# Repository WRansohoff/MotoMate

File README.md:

# "MotoMate" Handheld GPS Receiver

This is a small board designed to act as a handheld GPS receiver, and eventually (I hope) a handlebar-mounted GPS mapper / tracker for offroad motorcycling.

# Details

The microcontroller core is an STM32L496Rx chip - I recommend the STM32L496RGT3, because it costs less than $1 to get an extra 512KB of Flash (although the chip itself is more like $10). The 320KB of built-in RAM is enough to store a 150KB framebuffer for the 320x240 16bpp ILI9341 display, but it doesn't leave much room for storage-intensive algorithms such as image processing. Still, there's no external storage to worry about besides the microSD card.

The board is wired to use hardware periphererals for driving the SD/MMC interface, USB OTG, SPI for the display, and UART for talking to a "GY-NEO6MV2" GPS module. I've noticed that some listings for these u-blox Neo-6M-based GPS modules have red-colored boards with pinouts that won't work with this design; look for blue-colored ones and double-check the pinouts against the schematic. I might update the design to use the module itself instead of a cheap breakout board in the future, but for now, sorry for the inconvenience.

There's also a single-channel audio amplifier connected to one of the chip's DACs with a mute switch, and some ADCs are used to monitor a photodiode and the board's battery voltage. And there are pads exposed for an extra UART and I2C connection, and seven button inputs split across two tactile buttons and a 'navigation switch'. The buttons are assigned to pins so that there shouldn't be any conflicts with EXTI lines when setting up interrupts to listen for presses.

I'll write up more comprehensive information (and upload some proper gerber files) once I've had a chance to test this revision and upload some basic test firmwares to confirm the board's various functions.

# Schematic and Board Renders

# Previous Revision

I've assembled an earlier version of this design and confirmed that most parts of the design work, but I haven't written a comprehensive "GPS mapper" firmware yet. The first version has too much space between the TFT ribbon connector and the edge of the board to fold the display over the USB connector and mute switch, so it was awkward to handle. I hope that this version will fit together better, but I haven't received it yet for testing.

Sorry that I didn't get a better picture of the lit-up TFT; it's hard to take pictures of backlit displays, and it's not that important anyways. I also edited one of the images to remove the actual GPS coordinates, because I didn't feel like driving out to the middle of the woods to take a picture.

Anyways, so far I've tested (or not) the following parts:

* Battery monitoring: the 'charging' and 'done' LEDs seem to reflect the charge status, and the 12-bit ADC reads close to 4.2V on a full charge using the formula: `VBatt = ( ADC * 2 / 4095 ) * 3.3`. Note that for an accurate reading, you need to set one of the highest sampling times (250-650 cycles) due to the low amount of current flowing through the voltage divider.

* TFT display: The backlight can be adjusted with a PWM signal, and the SPI peripheral can be used with DMA to draw a framebuffer to the display. This makes it much easier to test other parts of the board :)

* GPS module: Appears to work, although I haven't tried configuring it with anything other than the default settings. After placing the antenna with a clear view of the sky and letting it acquire a few satellites, it reports latitude and longitude readings that appear to be accurate to within maybe 5 meters or so.

* microSD card: Not tested.

* Buttons: Tested using falling-edge interrupts with the pins configured as inputs with pull-up resistors enabled. These low-profile buttons are really designed to be used with a case that has plastic or rubber 'pegs' connected to larger buttons, though.

* Auxiliary UARTs and I2C: Not tested.

* 'Heartbeat' LED: Works.

* Photodiode: Not tested; in the first revision of the board, I put the photodiode underneath where the display's ribbon connector folded over, so it was always in darkness. D'oh!

* Speaker: Works well enough to play a sine wave accurately enough for a tuner to read the desired note. I haven't tried playing music or speech though, and it probably wouldn't do that very well. This is only a 12-bit DAC with poor filtering, after all. The speaker is mostly intended for beeps, buzzes, and chirps.

See `firmware/` for the source code used to run those tests, and `fw_lib/` for some shared helper functions.

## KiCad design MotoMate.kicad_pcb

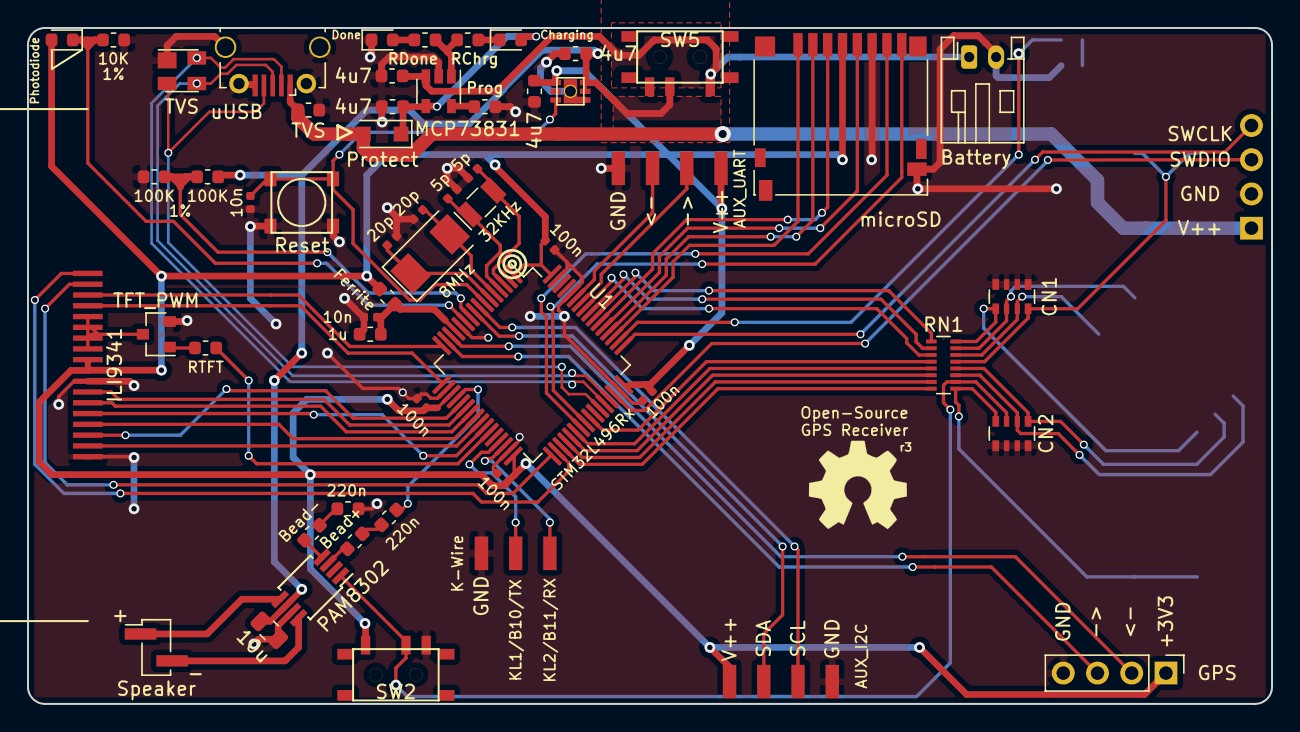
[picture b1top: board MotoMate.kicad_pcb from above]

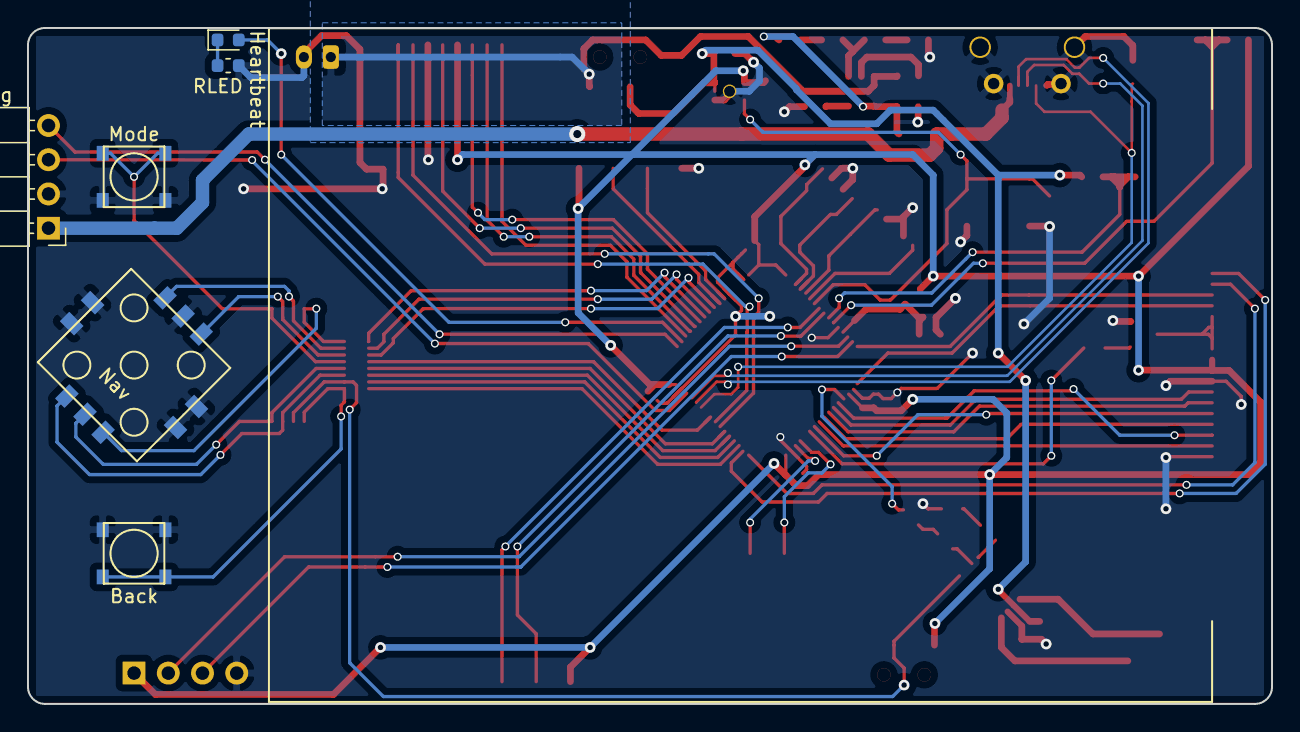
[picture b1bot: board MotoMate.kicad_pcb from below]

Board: 2 copper layers, 92.3 x 50.2 mm, 62 parts (6 on the bottom side), 75 nets.

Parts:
C1, C2, C19, C20: 4u7; C_0603_1608Metric
C3, C4, C5, C6: 100n; C_0402_1005Metric
C7, C13: 10n; C_0402_1005Metric
C8: 1u; C_0603_1608Metric
C9, C10: 20p; C_0402_1005Metric
C11, C12: 5p; C_0402_1005Metric
C16, C17: 220n; C_0603_1608Metric
C18: 10u; C_0805_2012Metric
CN1: Cin1; R_Array_Convex_4x0603
CN2: Cin2; R_Array_Convex_4x0603
D1: TVS; SOT-143
D2: Photodiode; LED_0603_1608Metric
D3: Heartbeat; LED_0603_1608Metric
D4: Protect; D_SOD-123F
D5: Charging; LED_0603_1608Metric
D6: Done; LED_0603_1608Metric
FB1: Ferrite; R_0603_1608Metric
FB2: Bead+; R_0603_1608Metric
FB3: Bead-; R_0603_1608Metric
J1: Prog; PinHeader_1x04_P2.54mm_Horizontal
J2: uUSB; MyMicroUSB
J3: microSD; microSD_HC_Hirose_DM3D-SF
J4: GPS; PinHeader_1x04_P2.54mm_Vertical
J5: AUX_UART; Conn_01x04_H_SMD
J6: AUX_I2C; Conn_01x04_H_SMD
J7: Battery; JST_PH_S2B-PH-K_1x02_P2.00mm_Horizontal
J8: ILI9341; ILI9341_18P_0.8mm
J9: K-Wire; Conn_01x03_H_SMD
LS1: Speaker; PinHeader_1x02_P2.00mm_Vertical_SMD_Pin1Left
Q1: TFT_PWM; SOT-23
R1: RTFT; R_0603_1608Metric
R2, R3: 100K; R_0603_1608Metric
R4: 10K; R_0603_1608Metric
R5: Prog; R_0603_1608Metric
R6: RChrg; R_0603_1608Metric
R7: RDone; R_0603_1608Metric
R8: RLED; R_0603_1608Metric
RN1: Rin; R_Array_Convex_8x0602
RV1: TVS; R_0603_1608Metric
SW1: Reset; Snap_Tac_Switch_SMT
SW2: Mute; mini_slide_switch
SW3: Mode; Snap_Tac_Switch_SMT
SW4: Back; Snap_Tac_Switch_SMT
SW5: On/Off; mini_slide_switch
SW6: Nav; NavSwitch_SMT
U1: STM32L496Rx; LQFP-64_10x10mm_P0.5mm
U2: LDFM33; ST_LDFM_2x2DFN
U3: PAM8302; MSOP-8_3x3mm_P0.65mm
U4: MCP73831; SOT-23-5
Y1: 8MHz; Crystal_SMD_Abracon_ABM3-2Pin_5.0x3.2mm
Y2: 32KHz; Crystal_SMD_EuroQuartz_EQ161-2Pin_3.2x1.5mm

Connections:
+5V: D4.2, J1.1, J2.1, RV1.1
+BATT: C20.1, J7.1, SW5.1, U4.3
Aux_RX: J5.2, U1.58
Aux_SCL: J6.3, U1.8
Aux_SDA: J6.2, U1.9
Aux_TX: J5.3, U1.59
Back: RN1.8, U1.35
BackR: CN2.8, RN1.9, SW4.1
Battery_Check: R2.1, R3.2, U1.10
GND: C1.2, C2.1, C3.2, C4.1, C5.1, C6.2, C7.1, C8.2, C9.2, C10.1, C11.2, C12.1, C13.2, C17.2, C18.2, C19.1, C20.2, CN1.1, CN1.2, CN1.3, CN1.4, CN2.1, CN2.2, CN2.3, CN2.4, D1.1, D6.1, J1.2, J2.5, J2.6, J3.6, J3.9, J4.4, J5.4, J6.4, J7.2, J8.1, J8.8, J9.3, Q1.2, R3.1, R4.2, R5.2, R8.2, RV1.2, SW1.1, SW2.3, SW3.2, SW4.2, SW6.6, U1.12, U1.18, U1.31, U1.47, U1.60, U1.63, U2.4, U2.7, U3.7, U4.2
GPS_RX: J4.2, U1.14
GPS_TX: J4.3, U1.15
Heartbeat: D3.2, U1.50
K-Line1: J9.2, U1.29
K-Line2: J9.1, U1.30
Light_Sensor: D2.1, R4.1, U1.11
Mode: RN1.4, U1.41
ModeR: CN1.8, RN1.13, SW3.1
Mute: RN1.7, U1.36
MuteR: CN2.7, RN1.10, SW2.2, U3.1
NavDR: CN1.6, RN1.15, SW6.4
NavLR: CN2.6, RN1.11, SW6.3
NavPR: CN2.5, RN1.12, SW6.2
NavRR: CN1.7, RN1.14, SW6.5
NavUR: CN1.5, RN1.16, SW6.1
Nav_D: RN1.2, U1.56
Nav_L: RN1.6, U1.37
Nav_P: RN1.5, U1.38
Nav_R: RN1.3, U1.57
Nav_U: RN1.1, U1.55
unnamed: C7.2, C8.1, FB1.1, U1.13
unnamed: C9.1, U1.6, Y1.1
unnamed: C10.2, U1.5, Y1.2
unnamed: C11.1, U1.4, Y2.1
unnamed: C12.2, U1.3, Y2.2
unnamed: C16.1, FB2.2
unnamed: C17.1, FB3.1
unnamed: D3.1, R8.1
unnamed: D5.1, R6.1
unnamed: D6.2, R7.1
unnamed: FB2.1, U3.3
unnamed: FB3.2, U3.4
unnamed: J8.11, J8.12, J8.13, J8.14, Q1.3
unnamed: LS1.1, U3.5
unnamed: LS1.2, U3.8
unnamed: Q1.1, R1.1
unnamed: R5.1, U4.5
unnamed: R6.2, R7.2, U4.1
Reset: C13.1, SW1.2, U1.7, U2.3
SD_CLK: J3.5, U1.53
SD_CMD: J3.3, U1.54
SD_D0: J3.7, U1.39
SD_D1: J3.8, U1.40
SD_D2: J3.1, U1.51
SD_D3: J3.2, U1.52
SWCLK: J1.4, U1.49
SWDIO: J1.3, U1.46
Speaker: C16.2, U1.20
TFT_CS: J8.5, U1.26
TFT_DC: J8.4, U1.24
TFT_PWM: R1.2, U1.27
TFT_RST: J8.2, U1.25
TFT_SCK: J8.3, U1.21
TFT_SDI: J8.6, U1.23
TFT_SDO: J8.7, U1.22
TFT_XL: J8.15, U1.17
TFT_XR: J8.17, U1.33
TFT_YD: J8.18, U1.34
TFT_YU: J8.16, U1.16
USB_D+: D1.3, J2.3, U1.45
USB_D-: D1.4, J2.2, U1.44
USB_ID: D1.2, J2.4, U1.43
VAA: C19.2, D4.1, D5.2, U4.4
VDD: C1.1, C3.1, C4.2, C5.2, C6.1, D2.2, FB1.2, J3.4, J4.1, J5.1, J6.1, J8.9, J8.10, SW2.1, U1.1, U1.19, U1.32, U1.48, U1.64, U2.1
VPP: C2.2, C18.1, R2.2, SW5.2, U2.5, U2.6, U3.6

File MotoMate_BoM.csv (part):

Part ID,Part type,Part size (Imperial),Part value,Example Digikey Item,Cost (qty: x),Comment
"C1, C2, C19, C20",Capacitor,0603,4.7 μF,https://www.digikey.com/short/p2hdqt,$0.68,Power supply decoupling capacitors for voltage regulator and battery charger. Use X5 or X7 ceramic capacitors rated for at least 6.3V (for 5V voltage inputs)
"C3, C4, C5, C6",Capacitor,0402,100 nF,https://www.digikey.com/short/p2hrz2,$0.40,Decoupling capacitors for the microcontroller / etc. Prefer X5 or X7 ceramic capacitors.
"C7, C13",Capacitor,0402,10 nF,https://www.digikey.com/short/p2hr54,$0.20,Decoupling capacitors for the reset button and analog voltage supply. Use X7 ceramic capacitors.
C8,Capacitor,0603,1 μF,https://www.digikey.com/short/pdhnbv,$0.10,Decoupling capacitor for the analog voltage supply. Use X7 ceramic capacitors.
"C9, C10",Capacitor,0402,20 pF,https://www.digikey.com/short/pdhnbj,$0.20,Decoupling capacitors for the high-speed external oscillator crystal. Actual values will depend on your crystal; 20pF is a rough estimate. Use C0G / NP0 ceramic capacitors.
"C11, C12",Capacitor,0402,5 pF,https://www.digikey.com/short/pdhnbc,$0.20,Decoupling capacitors for the low-speed external oscillator crystal. Actual values will depend on your crystal; 5pF is a rough estimate. Use C0G / NP0 capacitors.
"C14, C15, C16, C17",Capacitor,0603,220 nF,https://www.digikey.com/short/pdhnhv,$0.40,Filtering capacitors for the audio amplifier's input and output. Use X7 ceramic capacitors.
C18,Capacitor,0805,10 μF,https://www.digikey.com/short/pdhn55,$0.13,Power supply decoupling capacitor for the audio amplifier. Use X5 or X7 ceramic capacitors.
"CN1, CN2",Capacitor Network,0612,10 nF,https://www.digikey.com/short/pdhr2m,$0.64,Capacitor arrays for various debouncing filters. Values aren't too important; it's just to help prevent the microcontroller from incorrectly registering spurious button presses.
D1,TVS Diode Network,SOT-143-4,SP0503,https://www.digikey.com/short/pdhfqd,$0.82,3-in-1 TVS diodes for USB data line filtering. These diodes should protect the two differential data lines and the OTG 'ID' line.
D2,Photodiode,0603,ALS-PT19,https://www.digikey.com/short/pdhfq3,$0.43,Photodiode for detecting ambient light levels. I hope this can be used for automatic brightness adjustment.
D3,LED,0603,Any Color,https://www.digikey.com/short/p2hdpf,$0.14,"Heartbeat' LED, for basic testing and blinking."
D4,Schottky Diode,SOD-123,">= 10V, 1A",https://www.digikey.com/short/pdhw7b,$0.33,Schottky diode to protect against reverse polarity.
D5,LED,0603,Red,https://www.digikey.com/short/pdh21f,$0.14,"""Charging"" LED, lit up when the battery is charging."
D6,LED,0603,Green,https://www.digikey.com/short/pdh21m,$0.14,"""Done"" LED, lit up when the battery has finished charging."
FB1,Ferrite Bead,0603,N/A,https://www.digikey.com/short/p2h080,$0.10,Ferrite bead for filtering noise out of the analog voltage supply.
"FB2, FB3",Ferrite Bead,0603,N/A,https://www.digikey.com/short/p2h080,$0.20,Ferrite beads for filtering the audio amplifier's differential output.
J1,Pin Header,"0.1""",1x4,https://www.digikey.com/short/pdhw3q,$0.13,Programming / debugging header.
J2,USB Connector,Micro-B Socket,N/A,https://www.digikey.com/short/pdhw81,$2.07,"Micro-USB connector for battery charging and USB communication. I'm still working through a reel of cheap-o micro-B sockets that I ordered awhile ago, but they seem to fit the ""Wuerth_629105150521"" footprint in KiCAD."
J3,MicroSD Connector,Socket,Hirose DM3D-SF,https://www.digikey.com/short/pdh2z2,$1.75,"MicroSD card socket, for storing maps / images / routes / logs / etc."
J4,Pin Header,"0.1""",1x4,https://item.taobao.com/item.htm?id=40580284168,$2.50,"GPS breakout connector for a generic 4-pin uBlox Neo-6m GPS breakout board. This project is designed to fit a blue-colored ""GY-NEO6MV2"" breakout board, which is a cheap module that is widely available on eBay / Amazon / AliExpress / TaoBao / etc. These modules are much cheaper from Eastern listings than from Western ones. I've noticed that red-colored versions of this GPS module seem to have a different pinout that won't fit, so double-check the module's silkscreen markings against this project's schematic before you order one. Sorry that I can't link to a more reliable source; I can't endorse any particular third-party marketplace seller, including the one linked to here, and ordering from eBay-style sellers is never a completely sure bet. Maybe in the future I'll try to integrate the ublox module itself on the board."
"J5, J6",Pin Header,"0.1""",1x4,N/A,$0.00,Flat single-side connectors for auxiliary UART and I2C add-ons. Optional.
J7,JST Connector,PH-2,1x2,https://www.digikey.com/short/pdh24c,$0.17,"Battery connector - the JST PH-2 connector is popular among small lithium batteries, such as those sold by Adafruit. Double-check the polarity!"
J8,Flex Ribbon Connector,0.8 mm,1x18,https://item.taobao.com/item.htm?id=540901079780,$3.33,"Connector for an 18-pin / 0.8mm-pitch 2.8"" ILI9341 SPI TFT display with a resistive 'touch screen' overlay. These are cheap and widely-available from places like eBay / AliExpress / TaoBao / etc. DigiKey doesn't carry them, but using surplus 'off-brand' displays often saves about $10-20 per board for us hobbyists. Double-check the pinout against the listing you buy from, and consider using a different vendor or a forwarding service if you aren't familiar with ordering from TaoBao."
J9,Pin Header,"0.1""",1x3,N/A,$0.00,"Flat single-side 3-pin connector for adding a ""K-Wire"" interface board later on. My motorcycle uses this old standard which predates OBD-II, and while it is a 12V single-wire protocol, I hope to eventually make an adapter board which isolates 'transmit' and 'receive' signals for use with a UART peripheral."
LS1,Speaker,2-Wire,4 Ω,https://www.digikey.com/short/pdhnmp,$2.35,Speaker for the single-channel audio amplifier output.
Q1,Transistor,SOT-23,"NPN, BEC",https://www.digikey.com/short/pdhf4v,$0.12,Transistor to control the TFT display's backlight brightness using PWM.
R1,Resistor,0603,1 KΩ,https://www.digikey.com/short/p2hdw9,$0.10,"Base resistor for the TFT backlight control transistor. Value doesn't matter too much, keep it in the range of about 100Ω - 10KΩ"
"R2, R3",Resistor,0603,"100 KΩ, 1%",https://www.digikey.com/short/pdh2b7,$0.10,"Resistors for the voltage divider which lets the microcontroller read its own battery voltage. Use resistors with 1% precision, or choose two which have almost identical values."
R4,Resistor,0603,10 KΩ,https://www.digikey.com/short/pdh29r,$0.10,"Resistor which lets the microcontroller read an analog voltage from its photodiode input. Prefer resistors with 1% precision, but you'll probably have to calibrate the brightness reading anyways since photodiodes aren't very precise."
R5,Resistor,0603,">= 2 KΩ, 1%",https://www.digikey.com/short/pdh2b4,$0.10,"This resistor sets the rate of charge for the battery charger. Charge current = 1000 / R, so use 2KΩ for a 500mA charge rate, 10KΩ for a 100mA charge rate, etc. 500mA is the maximum charge rate. Use resistors with 1% precision to ensure you get the right charge rate."
"R6, R7, R8",Resistor,0603,220Ω - 4.7KΩ,https://www.digikey.com/short/p2hdw9,$0.30,"Current-limiting resistors for the ""charging"", ""done charging"", and ""heartbeat"" LEDs. Use higher values to make the LEDs dimmer."
RN1,Resistor Network,1506,1 KΩ,https://www.digikey.com/short/pdhr1z,$0.29,Resistor array for various debouncing filters. Value isn't too important; it's just to help prevent the microcontroller from reading spurious button presses.
RV1,Varistor,0603,5.5V (7.1V-9.3V),https://www.digikey.com/short/pdhrv3,$0.48,"TVS varistor for the +5V power line. It should serve a similar function to the TVS diodes on the data lines, protecting the system from Transient Voltage surges."
SW1,Tactile Button,SMD,SPST,https://www.digikey.com/short/pdhr0w,$0.22,Reset button.
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
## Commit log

2019-10-25 Add an initial Readme.
2019-10-25 Add custom schematic symbols and footprints.
2019-10-25 Add 'library table' files.
2019-10-25 Add Bill of Materials.
2019-10-25 Add project / schematic / PCB files.
2019-10-25 Add a few render files.
2019-10-25 Fix Readme headings and add renders.
2019-10-25 Round off a power trace that wound up with a weird 'elbow' shape somehow.
2019-10-25 Update renders.
2019-10-25 Add pictures of the previous revision for an idea of how everything fits together.
2019-10-25 Add some simple supporting methods to configure peripherals for use with the board and interact with on-board devices.
2019-10-25 Add directory for test firmware examples.
2019-10-25 Add directories for not-yet-working test projects: buttons, SD card, and touch screen.
2019-10-25 Add test firmware to monitor the ADC channel connected to the battery voltage.
2019-10-25 Add test firmware for playing a single tone on the speaker.
2019-10-25 Add test firmware for controlling the TFT display's backlight brightness.
2019-10-25 Add test firmware for drawing to the TFT display through a DMA-ferried framebuffer.
2019-10-25 Add test firmware for listening to the GPS module and printing its raw output to the TFT display.
2019-10-25 Update Readme now that some example firmware projects exist.
2019-10-26 Fix Makefiles to reflect the current directory structure.
2019-10-28 Minor comment fixes in the GPS test firmware.
2019-10-28 Add a simple firmware to test the button inputs.
2019-10-28 Add an outline of a combined 'test suite' firmware which will combine tests for different parts of the board into one firmware image.
2019-10-28 Move preliminary UART functions into some simple BSP files.
2019-10-28 Move the board initialization steps into a common 'board_init' BSP function. It would be nice to decouple the actual pin connections on the board from the functions like 'draw', 'check GPS location',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
2019-10-28 Start to prepare the 'test suite' firmware for having a menu of different tests.
2019-10-28 Add a 'globals' header file to hold definitions which need to be accessible from pretty much everywhere, and start setting up a menu system.
2019-10-28 Implement a simple menu system.
2019-10-28 Improve main loop and display transfers. Instead of periodically refreshing, it now waits for a condition that merits a display update before performing one, and it avoids drawing to the framebuffer 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
2019-10-28 Outline a few more test menu items.
2019-10-28 Start adding initialization of audio data/peripherals to the shared firmware.
2019-10-28 Update legacy test firmwares to reflect HAL changes.
2019-10-29 Adjust string/character-drawing boundary checks.
2019-10-29 Make the main menu remember its cursor position.
2019-10-29 Fix 'tft_display' test firmware build.
2019-10-29 Readme update to reflect recent test suite progress.
2019-10-29 Add a missing link to the 'mute' slide switch part in the bill of materials - whoops!
2019-10-29 Move common application-level definitions into a 'global' source file.
2019-10-29 Implement brightness control test menu. I really need to move the input handling out of the interrupt handlers...
2019-10-29 Add font glyphs for '%', ',', '(', ')'
2019-10-29 Move the display re-drawing logic into a separate 'application' file.
2019-10-29 Move button-press logic out of interrupt handlers and into the 'application code' files.
2019-10-29 Start to outline a 'battery reading' test, and some minor formatting.
2019-10-29 Add left/right arrows to the 'display brightness' test.
2019-10-29 Fill out the audio test menu display, minus the 'mute?' option.
2019-10-29 Add ADC initialization and outline 'battery check' test.
2019-10-29 Add a menu item for testing the touch screen.
2019-10-29 Implement basic 'battery check' test, add a menu selector to the audio test menu, and add a menu item for a future 'touch screen' test.
2019-10-30 Add scaffolding to auto-generate documentation using Sphinx.
2019-10-30 Add autodocs for the 'global.h' file. It looks like it prints arrays with the post-preprocessor number of elements, but otherwise this seems promising.
2019-10-30 Fix autodoc generation: it looks like it doesn't handle 'int x, y;' gracefully.
2019-10-30 Add a little more information to the firmware documentation readme.
2019-12-15 Update the QFP chip footprint to have longer pads for easier soldering. Simplify the audio amp circuit. Use a smaller power switch and put it closer to the power supply. Switch voltage regulators to 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
2019-12-15 Re-add the OSHW logo
2019-12-15 Round PCB corners.
2019-12-16 Update schematic for the new voltage regulator.
2019-12-16 Update bill of materials for the third (still untested) revision.
